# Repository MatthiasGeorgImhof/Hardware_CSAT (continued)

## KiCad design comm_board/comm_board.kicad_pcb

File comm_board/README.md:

# Communication Board #

Communication board with ethernet and radio operating in the US ISM band of 915MHz. Check your jurisdiction about availability of this band!

- STM32L496 microprocessor
- TI CC1101 transceiver for 915MHz oeration and TI CC1190 power frontend
- Ethernet modem

OpenLST Reference Hardware

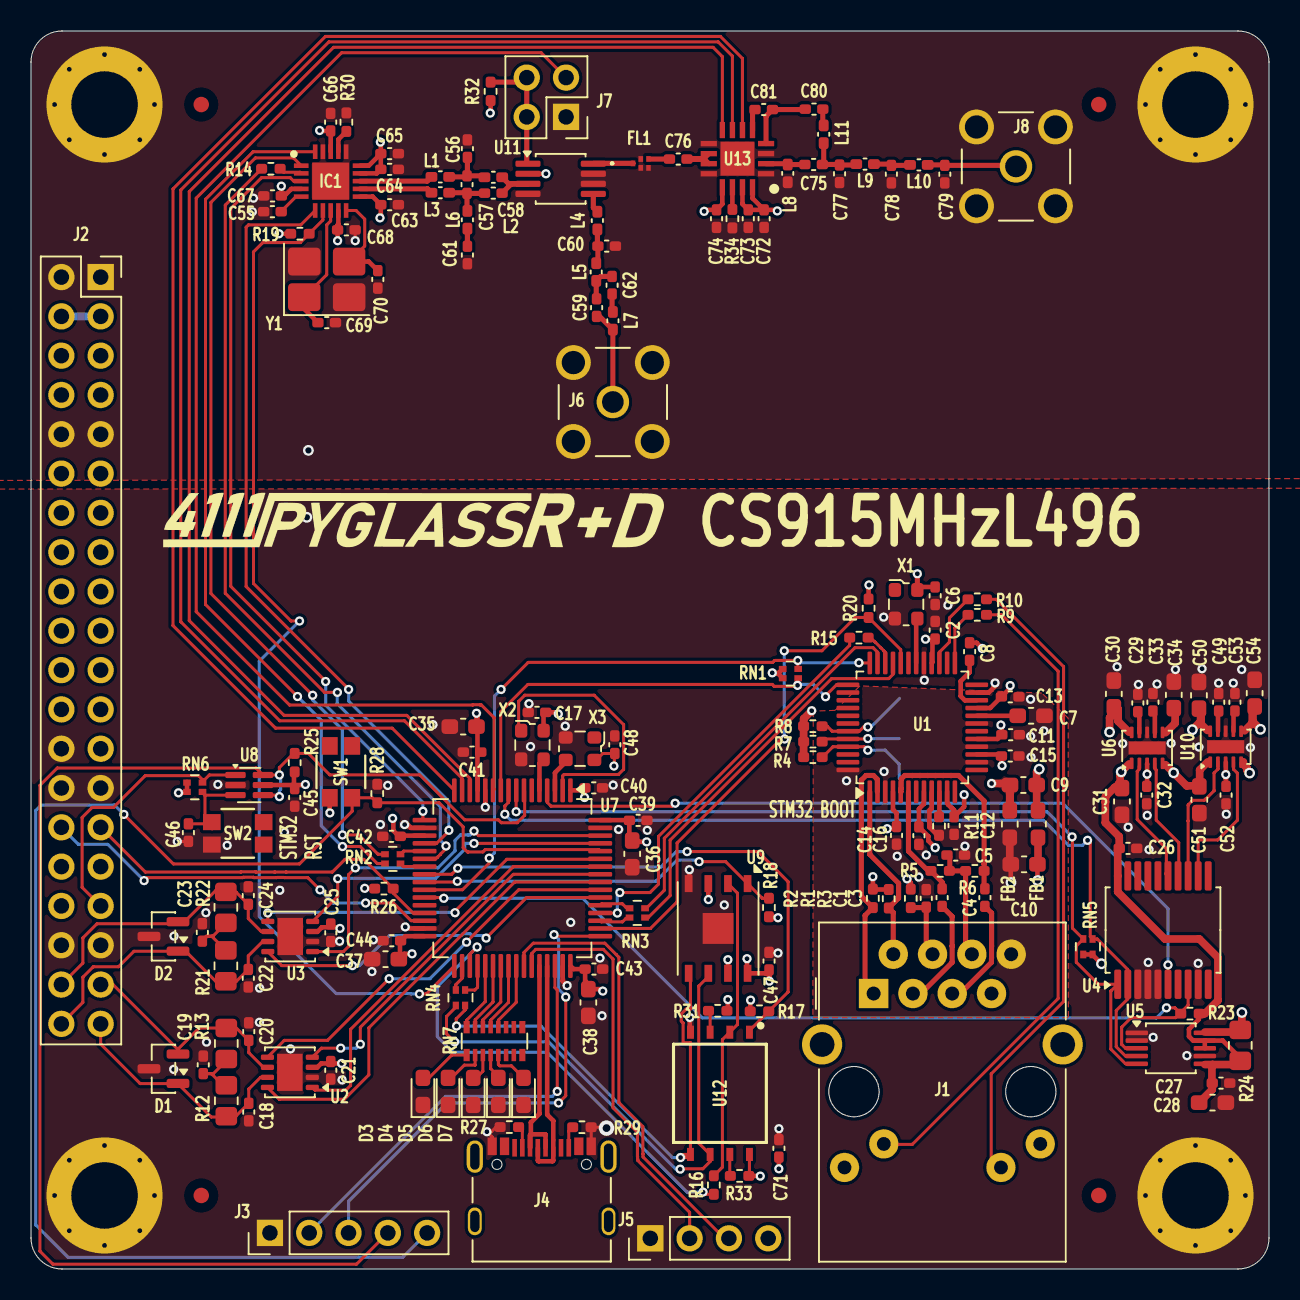
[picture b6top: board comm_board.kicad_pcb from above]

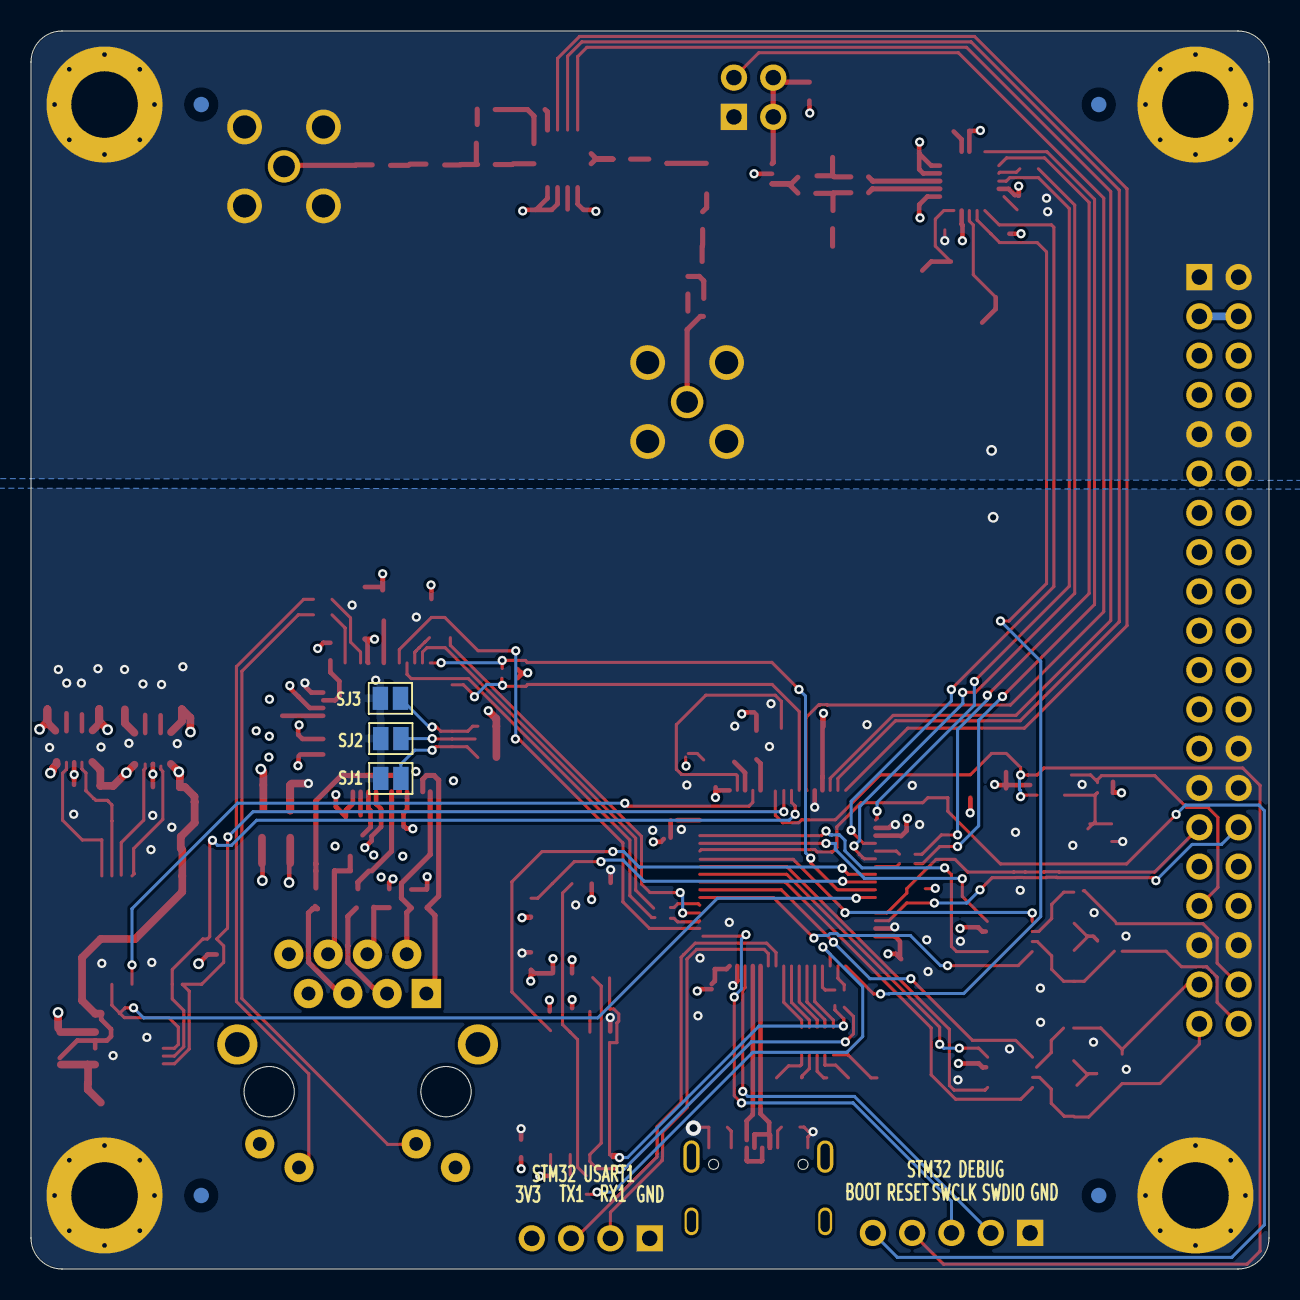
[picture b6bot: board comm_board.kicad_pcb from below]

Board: 4 copper layers, 80.0 x 80.0 mm, 186 parts (7 on the bottom side), 143 nets.

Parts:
C1, C5: 10nF; C_0402_1005Metric_Pad0.74x0.62mm_HandSolder
C2, C6, C8, C11, C12, C13, C14, C15, C16, C17, C21, C25, C26, C27, C32, C39, C40, C41, C42, C43, C44, C45, C46, C47, C48, C52, C71: 100nF; C_0402_1005Metric_Pad0.74x0.62mm_HandSolder
C3, C4: 6.8nF; C_0402_1005Metric_Pad0.74x0.62mm_HandSolder
C7, C9, C10, C28, C30, C34, C35, C36, C37, C38, C50, C54: 10uF; C_0603_1608Metric_Pad1.08x0.95mm_HandSolder
C18, C20, C22, C24: 100pF; C_0402_1005Metric_Pad0.74x0.62mm_HandSolder
C19, C23: 4nF7; C_0402_1005Metric_Pad0.74x0.62mm_HandSolder
C29, C33, C49, C53: 220pF; C_0402_1005Metric_Pad0.74x0.62mm_HandSolder
C31, C51: 22uF; C_0603_1608Metric_Pad1.08x0.95mm_HandSolder
C55, C61, C63, C64, C65, C66, C67, C68, C72, C73, C74: 100n; C_0402_1005Metric_Pad0.74x0.62mm_HandSolder
C56, C58, C59, C62: 1p5; C_0402_1005Metric_Pad0.74x0.62mm_HandSolder
C57: 1p; C_0402_1005Metric_Pad0.74x0.62mm_HandSolder
C60, C77: 3p3; C_0402_1005Metric_Pad0.74x0.62mm_HandSolder
C69, C70: 27p; C_0402_1005Metric_Pad0.74x0.62mm_HandSolder
C75, C76: 47p; C_0402_1005Metric_Pad0.74x0.62mm_HandSolder
C78: 8p2; C_0402_1005Metric_Pad0.74x0.62mm_HandSolder
C79: 0p5; C_0402_1005Metric_Pad0.74x0.62mm_HandSolder
C80, C81: 12p; C_0402_1005Metric_Pad0.74x0.62mm_HandSolder
D1, D2: NUP2105LT1G; SOT-23
D3: RED; LED_0603_1608Metric_Pad1.05x0.95mm_HandSolder
D4: GREEN; LED_0603_1608Metric_Pad1.05x0.95mm_HandSolder
D5, D6, D7: YELLOW; LED_0603_1608Metric_Pad1.05x0.95mm_HandSolder
FB1, FB2: 1K; L_0603_1608Metric_Pad1.05x0.95mm_HandSolder
FID1, FID2, FID3, FID4, FID5, FID6, FID7, FID8: Fiducial; Fiducial_1mm_Mask2mm
FL1: B39921B2672P810
H1, H2, H3, H4: MountingHole_Pad; MountingHole_4.3mm_M4_Pad_Via_Custom
IC1: CC1101RGPR; QFN50P400X400X100-21N-D
J1: RJ45_Amphenol_RJMG1BD3B8K1ANR
J2: PC104 Conn_02x20_Odd_Even; PinSocket_2x20_P2.54mm_Vertical
J3: Conn_01x05_Pin Vertical; PinHeader_1x05_P2.54mm_Vertical
J4: 10155435-00011LF; AMPHENOL_10155435-00011LF
J5: Conn_01x04_Pin Vertical; PinHeader_1x04_P2.54mm_Vertical
J6, J8: SMA Jack; LINX_CONSMA001-G
J7: Conn_02x03_Odd_Even; PinHeader_2x02_P2.54mm_Vertical
L1, L3, L4, L5, L7: 12n; L_0402_1005Metric_Pad0.77x0.64mm_HandSolder
L2, L6: 18n; L_0402_1005Metric_Pad0.77x0.64mm_HandSolder
L8: 10n; L_0402_1005Metric_Pad0.77x0.64mm_HandSolder
L9: 2n2; L_0402_1005Metric_Pad0.77x0.64mm_HandSolder
L10: 3n9; L_0402_1005Metric_Pad0.77x0.64mm_HandSolder
L11: 7n5; L_0402_1005Metric_Pad0.77x0.64mm_HandSolder
R1, R2, R5, R6: 49R9; R_0402_1005Metric_Pad0.72x0.64mm_HandSolder
R3: 10R; R_0402_1005Metric_Pad0.72x0.64mm_HandSolder
R4, R7, R8: 10K; R_0402_1005Metric_Pad0.72x0.64mm_HandSolder
R9, R10: 470R; R_0402_1005Metric_Pad0.72x0.64mm_HandSolder
R11: 12K4; R_0402_1005Metric_Pad0.72x0.64mm_HandSolder
R12, R13, R21, R22: 60R4; R_0805_2012Metric_Pad1.20x1.40mm_HandSolder
R14, R15, R16: 22R; R_0402_1005Metric_Pad0.72x0.64mm_HandSolder
R17, R18, R19, R20, R23, R25, R28, R31, R32, R33: 100K; R_0402_1005Metric_Pad0.72x0.64mm_HandSolder
R24: 10m; R_0805_2012Metric_Pad1.20x1.40mm_HandSolder
R26: 330K; R_0402_1005Metric_Pad0.72x0.64mm_HandSolder
R27, R29: 5K1; R_0402_1005Metric_Pad0.72x0.64mm_HandSolder
R30: 56K; R_0402_1005Metric_Pad0.72x0.64mm_HandSolder
R34: 3K3; R_0402_1005Metric_Pad0.72x0.64mm_HandSolder
RN1: 10K; R_Array_Convex_2x0402_widepads
RN2, RN3, RN4: 22R; R_Array_Convex_2x0402_widepads
RN5: 5K6; R_Array_Convex_2x0402_widepads
RN6: 100K; R_Array_Convex_2x0402_widepads
RN7: 1K; R_Array_Convex_8x0602_widepads
SJ1, SJ2, SJ3: SOLDERJUMPERREFLOW_NOPASTE; SolderJumper-2_P1.3mm_Open_Pad1.0x1.5mm
SW1, SW2: EVP-AA602W; EVP602AA
U1: W5500; LQFP-48_7x7mm_P0.5mm
U2, U3: TCAN3414; VSON-8-1EP_3x3mm_P0.65mm_EP1.65x2.4mm
U4: MCP23008T-E/SS; SSOP-20_5.3x7.2mm_P0.65mm
U5: INA226AIDGSR; VSSOP-10_3x3mm_P0.5mm
U6, U10: TPS22968QDMGRQ1; WSON-10-1EP_2x3mm_P0.5mm_EP0.84x2.4mm
U7: STM32L496RGTx; LQFP-64_10x10mm_P0.5mm
U8: 74LVC2G07; SOT-363_SC-70-6
U9: MR25H10; DFN-8-1EP_6x5mm_P1.27mm_EP2x2mm
U11: PE4250MLI; MSOP-8_3x3mm_P0.65mm
U12: MT29F4G01ABAFDWB-IT:F TR; SON127P800X600X65-8N
U13: CC1190RGVR; QFN65P400X400X100-17N-D
X1: 25MHz; Oscillator_SMD_ECS_2520MV-xxx-xx-4Pin_2.5x2.0mm
X2: 10MHz; Oscillator_SMD_ECS_2520MV-xxx-xx-4Pin_2.5x2.0mm
X3: 32.768KHZ; Oscillator_SMD_ECS_2520MV-xxx-xx-4Pin_2.5x2.0mm
Y1: 26MHz; Crystal_SMD_3225-4Pin_3.2x2.5mm_HandSoldering

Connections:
/3V3_AUX: J2.15, R24.1, U5.10 (IN+)
/3V3_BRIDGE: C17.1, C21.1, C25.1, C35.1, C36.1, C37.1, C38.1, C39.1, C40.1, C41.1, C42.1, C43.1, C44.1, C45.2, C48.1, J2.13, J5.4, R25.1, R26.1, RN5.3 (R2.2), RN5.4 (R1.2), RN6.1 (R1.1), RN6.2 (R2.1), SW1.1, U2.3 (VCC), U3.3 (VCC), U7.1 (VBAT), U7.13 (VDDA), U7.19 (VDD), U7.32 (VDD), U7.48 (VDDUSB), U7.64 (VDD), U8.5 (VCC), X2.4 (VDD), X3.4 (VCC)
/3V3_COMM: C54.2, C63.1, C64.1, C65.1, C66.1, C67.1, C68.1, IC1.4 (DVDD), IC1.9 (AVDD_1), IC1.11 (AVDD_2), IC1.14 (AVDD_3), IC1.15 (AVDD_4), IC1.18 (DGUARD), R19.1, R32.1, U10.6 (VOUT2), U11.2 (V1)
/3V3_LAN: C2.1, C6.1, C9.1, C30.1, FB1.1, J1.L1, J1.L4, R4.1, R7.1, R8.1, R20.1, RN1.3 (R2.2), RN1.4 (R1.2), U1.28 (VDD), U6.10 (VOUT1), X1.4 (VCC)
/CAN Bridge/3V3_MRAM: C47.1, C50.1, C71.1, R17.1, R18.1, R31.1, R33.1, U9.3 (~WP), U9.7 (~HOLD), U9.8 (VDD), U10.10 (VOUT1), U12.8 (VCC)
/CAN Bridge/CAN1_H: C22.1, D2.1 (K), J2.40, R21.1, U3.7 (CANH)
/CAN Bridge/CAN1_L: C24.2, D2.2 (K), J2.38, R22.2, U3.6 (CANL)
/CAN Bridge/CAN2_H: C18.1, D1.1 (K), J2.39, R12.1, U2.7 (CANH)
/CAN Bridge/CAN2_L: C20.2, D1.2 (K), J2.37, R13.2, U2.6 (CANL)
/CAN Bridge/COMM1_RST: J2.33, RN6.4 (R1.2), U8.1 (IN1)
/CAN Bridge/Flash/SPI_CLK: RN4.1 (R1.1), U9.6 (SCK), U12.6 (SCK)
/CAN Bridge/Flash/SPI_MISO: R16.1, U9.2 (SO), U12.2 (SO/IO1)
/CAN Bridge/Flash/SPI_MOSI: RN4.2 (R2.1), U9.5 (SI), U12.5 (SI/IO0)
/CAN Bridge/I2C2_SCL: RN5.2 (R2.1), U4.1 (SCL), U5.5 (SCL), U7.8 (PC0)
/CAN Bridge/I2C2_SDA: RN5.1 (R1.1), U4.2 (SDA), U5.4 (SDA), U7.9 (PC1)
/CAN Bridge/PMIC/BOOT: J3.5, R28.1, SW1.2, U7.60 (PH3_BOOT0)
/CAN Bridge/PMIC/CAN1_RX: U3.4 (RXD), U7.61 (PB8)
/CAN Bridge/PMIC/CAN1_SHDN: U3.5 (SHTD), U7.59 (PB7)
/CAN Bridge/PMIC/CAN1_STB: U3.8 (STB), U7.54 (PD2)
/CAN Bridge/PMIC/CAN1_TX: U3.1 (TXD), U7.62 (PB9)
/CAN Bridge/PMIC/CAN2_RX: U2.4 (RXD), U7.57 (PB5)
/CAN Bridge/PMIC/CAN2_SHDN: U2.5 (SHTD), U7.55 (PB3)
/CAN Bridge/PMIC/CAN2_STB: U2.8 (STB), U7.56 (PB4)
/CAN Bridge/PMIC/CAN2_TX: U2.1 (TXD), U7.58 (PB6)
/CAN Bridge/PMIC/EXTI0: RN1.2 (R2.1), U1.36 (~INT), U7.26 (PB0)
/CAN Bridge/PMIC/EXTI3: IC1.3 (GDO2), U7.17 (PA3)
/CAN Bridge/PMIC/EXTI4: IC1.6 (GDO0_(ATEST)), U7.20 (PA4)
/CAN Bridge/PMIC/EXTI10: J2.29, R26.2, U7.29 (PB10)
/CAN Bridge/PMIC/EXTI11: J2.30, U7.30 (PB11)
/CAN Bridge/PMIC/FS_DN: J4.A7 (DN1_A), J4.B7 (DN2_B), U7.44 (PA11)
/CAN Bridge/PMIC/FS_DP: J4.A6 (DP1_A), J4.B6 (DP2_B), U7.45 (PA12)
/CAN Bridge/PMIC/HSE_EN: U7.2 (PC13), X2.1 (TRI-STATE)
/CAN Bridge/PMIC/HSE_IN: U7.5 (PH0), X2.3 (OUTPUT)
/CAN Bridge/PMIC/LED1: RN7.16 (R), U7.37 (PC6)
/CAN Bridge/PMIC/LED2: RN7.15 (R), U7.38 (PC7)
/CAN Bridge/PMIC/LED3: RN7.14 (R), U7.39 (PC8)
/CAN Bridge/PMIC/LED4: RN7.13 (R), U7.40 (PC9)
/CAN Bridge/PMIC/LED5: RN7.12 (R), U7.41 (PA8)
/CAN Bridge/PMIC/NRST: J3.4, R25.2, U7.7 (NRST), U8.4 (OUT2), U8.6 (OUT1)
/CAN Bridge/PMIC/OSC32_IN: U7.3 (PC14), X3.3 (OUT)
/CAN Bridge/PMIC/PA0: U7.14 (PA0), U13.8 (PA_EN)
/CAN Bridge/PMIC/PA1: U7.15 (PA1), U13.7 (LNA_EN)
/CAN Bridge/PMIC/PA2: U7.16 (PA2), U13.6 (HGM)
/CAN Bridge/PMIC/PC2: RN1.1 (R1.1), U1.37 (~RST), U7.10 (PC2)
/CAN Bridge/PMIC/PC3: J7.3, U7.11 (PC3)
/CAN Bridge/PMIC/RESET: C46.1, RN6.3 (R2.2), SW2.3, U8.3 (IN2)
/CAN Bridge/PMIC/SPI1_MISO: R14.2, U7.22 (PA6)
/CAN Bridge/PMIC/SPI1_MOSI: RN2.3 (R2.2), U7.23 (PA7)
/CAN Bridge/PMIC/SPI1_SCK: RN2.4 (R1.2), U7.21 (PA5)
/CAN Bridge/PMIC/SPI2_MISO: R16.2, U7.35 (PB14)
/CAN Bridge/PMIC/SPI2_MOSI: RN4.3 (R2.2), U7.36 (PB15)
/CAN Bridge/PMIC/SPI2_SCK: RN4.4 (R1.2), U7.34 (PB13)
/CAN Bridge/PMIC/SPI3_MISO: R15.1, U7.52 (PC11)
/CAN Bridge/PMIC/SPI3_MOSI: RN3.3 (R2.2), U7.53 (PC12)
/CAN Bridge/PMIC/SPI3_SCK: RN3.4 (R1.2), U7.51 (PC10)
/CAN Bridge/PMIC/SYS_JTMS_SWCLK: J3.3, U7.49 (PA14)
/CAN Bridge/PMIC/SYS_JTMS_SWDIO: J3.2, U7.46 (PA13)
/CAN Bridge/PMIC/USART1_RX: J5.2, U7.43 (PA10)
/CAN Bridge/PMIC/USART1_TX: J5.3, U7.42 (PA9)
/CAN Bridge/Power Switch/ENABLE0: U4.12 (GP0), U10.4 (ON2)
/CAN Bridge/Power Switch/ENABLE1: U4.13 (GP1), U10.2 (ON1)
/CAN Bridge/Power Switch/ENABLE2: U4.14 (GP2), U6.4 (ON2)
/CAN Bridge/Power Switch/ENABLE3: U4.15 (GP3), U6.2 (ON1)
/CAN Bridge/Power Switch/VBUS: C26.1, C27.1, C28.1, C31.1, C32.1, C51.1, C52.1, R23.1, R24.2, U4.20 (VDD), U5.6 (VS), U5.8 (VBUS), U5.9 (IN-), U6.1 (VIN1), U6.3 (VBIAS), U6.5 (VIN2), U10.1 (VIN1), U10.3 (VBIAS), U10.5 (VIN2)
/CAN Bridge/Power Switch/VOUT2: C34.2, U6.6 (VOUT2)
/CAN Bridge/Power_INT: R23.2, U4.8 (INT), U5.3 (ALERT), U7.27 (PB1)
/CAN Bridge/Power_RST: U4.6 (*RESET), U7.4 (PC15)
/CAN Bridge/SPI_FLASH_CS: R17.2, U7.24 (PC4), U12.1 (CS#)
/CAN Bridge/SPI_LAN_CS: R20.2, U1.32 (~SCS), U7.50 (PA15)
/CAN Bridge/SPI_LAN_MISO: R15.2, U1.34 (MISO)
/CAN Bridge/SPI_LAN_MOSI: RN3.2 (R2.1), U1.35 (MOSI)
/CAN Bridge/SPI_LAN_SCK: RN3.1 (R1.1), U1.33 (SCLK)
/CAN Bridge/SPI_MRAM_CS: R18.2, U7.25 (PC5), U9.1 (~CS)
/CAN Bridge/SPI_RF_CS: IC1.7 (CSN), R19.2, U7.33 (PB12)
/CAN Bridge/SPI_RF_MISO: IC1.2 (SO_(GDO1)), R14.1
/CAN Bridge/SPI_RF_MOSI: IC1.20 (SI), RN2.2 (R2.1)
/CAN Bridge/SPI_RF_SCK: IC1.1 (SCLK), RN2.1 (R1.1)
/GND: C2.2, C6.2, C9.2, C17.2, C18.2, C19.2, C20.1, C21.2, C22.2, C23.2, C24.1, C25.2, C26.2, C27.2, C28.2, C29.2, C30.2, C31.2, C32.2, C33.1, C34.1, C35.2, C36.2, C37.2, C38.2, C39.2, C40.2, C41.2, C42.2, C43.2, C44.2, C45.1, C46.2, C47.2, C48.2, C49.2, C50.2, C51.2, C52.2, C53.1, C54.1, C55.2, C56.1, C60.2, C61.2, C63.2, C64.2, C65.2, C66.2, C67.2, C68.2, C69.2, C70.2, C71.2, C72.2, C73.2, C74.2, C77.2, C78.2, C79.2, D1.3 (A), D2.3 (A), D3.1 (K), D4.1 (K), D5.1 (K), D6.1 (K), D7.1 (K), FB2.1, FL1.2 (GROUND_1), FL1.3 (GROUND_2), FL1.5 (GROUND_3), H1.1, H2.1, H3.1, H4.1, IC1.16 (GND_1), IC1.19 (GND_2), IC1.21 (GND_3), J2.1, J2.2, J2.9, J2.10, J2.26, J2.27, J2.28, J2.35, J2.36, J3.1, J4.A1_B12 (GND), J4.B1_A12 (GND__1), J5.1, J6.2 (Ext), J7.1, J8.2 (Ext), L8.1, R27.1, R28.2, R29.1, R30.2, R34.2, SJ1.2 (B), SJ2.2 (B), SJ3.2 (B), SW2.4, U1.23 (RSVD), U1.29 (GND), U2.2 (GND), U2.9 (GND), U3.2 (GND), U3.9 (GND), U4.3 (A2), U4.4 (A1), U4.5 (A0), U4.9 (VSS), U5.1 (A1), U5.2 (A0), U5.7 (GND), U6.8 (GND), U6.11 (TPAD), U7.12 (VSSA), U7.18 (VSS), U7.31 (VSS), U7.47 (VSS), U7.63 (VSS), U8.2 (GND), U9.4 (VSS), U9.9 (PAD), U10.8 (GND), U10.11 (TPAD), U11.4 (N/C_OR_GND), U11.6 (GND_1), U11.7 (GND_2), U12.4 (VSS), U13.1 (GND_1), U13.3 (GND_2), U13.9 (GND_3), U13.12 (GND_4), U13.17 (GND_5), X1.2 (GND), X2.2 (GND), X3.2 (GND), Y1.2 (G), Y1.4 (G)
/INTERBOARD_CONNECTOR2/BATT: J2.3, J2.4
/PW_RF_915MHz/RF_INOUT: FL1.1 (INPUT), U11.8 (RF2)
/SPI_LAN/AGND: C1.2, C5.2, C7.2, C8.2, C10.2, C11.2, C12.2, C13.2, C14.2, C15.2, C16.2, FB2.2, J1.R8, R11.2, U1.3 (AGND), U1.9 (AGND), U1.14 (AGND), U1.16 (AGND), U1.19 (AGND), U1.48 (AGND)
/SPI_LAN/AVDD: C10.1, C11.1, C12.1, C13.1, C14.1, C15.1, C16.1, FB1.2, R1.1, R2.1, R3.1, U1.4 (AVDD), U1.8 (AVDD), U1.11 (AVDD), U1.15 (AVDD), U1.17 (AVDD), U1.21 (AVDD)
/SPI_LAN/GREENLED: J1.L3, R9.1
/SPI_LAN/RX+: C3.2, R5.2, U1.6 (RXP)
/SPI_LAN/RX-: C4.2, R6.2, U1.5 (RXN)
/SPI_LAN/TX+: J1.R1 (TD+), R2.2, U1.2 (TXP)
/SPI_LAN/TX-: J1.R2 (TD-), R1.2, U1.1 (TXN)
/SPI_LAN/YELLOWLED: J1.L2, R10.1
/VRF: C72.1, C73.1, C74.1, J2.5, U13.13 (VDD_LNA), U13.15 (VDD_PA2), U13.16 (VDD_PA1)
unnamed: C19.1, R12.2, R13.1
unnamed: C23.1, R21.2, R22.1
unnamed: C56.2, C57.1, L1.2, L2.1
unnamed: C57.2, C58.1, L3.2, L6.1
unnamed: C59.1, C62.1, L5.2
unnamed: C60.1, L4.2, L5.1
unnamed: C61.1, L6.2
unnamed: C62.2, L7.1
unnamed: C75.2, C77.1, L9.1, L11.1
unnamed: C78.1, L9.2, L10.1
unnamed: C80.1, L11.2
unnamed: D3.2 (A), RN7.1 (R)
unnamed: D4.2 (A), RN7.2 (R)
unnamed: D5.2 (A), RN7.3 (R)
unnamed: D6.2 (A), RN7.4 (R)
unnamed: D7.2 (A), RN7.5 (R)
unnamed: C76.1, FL1.4 (OUTPUT)
unnamed: C55.1, IC1.5 (DCOUPL)
unnamed: IC1.17 (RBIAS), R30.1
unnamed: IC1.13 (RF_N), L1.1
unnamed: IC1.12 (RF_P), L3.1
unnamed: C69.1, IC1.8 (XOSC_Q1), Y1.1
unnamed: C70.1, IC1.10 (XOSC_Q2), Y1.3
unnamed: C4.1, J1.R5 (RCT)
unnamed: C3.1, J1.R3 (RD+)
unnamed: C5.1, J1.R6 (RD-), R5.1, R6.1
unnamed: C1.1, J1.R4 (TCT), R3.2
unnamed: J4.A5 (CC1_A), R27.2
unnamed: J4.B5 (CC2_B), R29.2
unnamed: C59.2, J6.1 (In), L7.2
unnamed: J7.2, J7.4, R32.2, U11.1 (V2/DIR)
unnamed: C79.1, J8.1 (In), L10.2
unnamed: R4.2, SJ1.1 (A), U1.45 (PMODE0)
unnamed: R7.2, SJ2.1 (A), U1.44 (PMODE1)
unnamed: R8.2, SJ3.1 (A), U1.43 (PMODE2)
unnamed: C8.1, U1.22 (1V2O)
unnamed: R10.2, U1.27 (ACTLED)
unnamed: R11.1, U1.10 (EXRES1)
unnamed: R9.2, U1.25 (LINKLED)
unnamed: C7.1, U1.20 (TOCAP)
unnamed: U1.30 (XI/CLKIN), X1.3 (OUT)
unnamed: C29.1, U6.9 (CT1)
unnamed: C33.2, U6.7 (CT2)
unnamed: C49.1, U10.9 (CT1)
unnamed: C53.2, U10.7 (CT2)
unnamed: L4.1, U11.5 (RF1)
unnamed: C58.2, L2.2, U11.3 (RFC)
unnamed: R33.2, U12.7 (HOLD#/IO3)
unnamed: R31.2, U12.3 (WP#/IO2)
unnamed: R34.1, U13.14 (BIAS)
unnamed: C81.1, U13.5 (LNA_IN)
unnamed: C76.2, U13.10 (LNA_OUT), U13.11 (PA_IN)
unnamed: C75.1, L8.2, U13.2 (PA_OUT)
unnamed: C80.2, C81.2, U13.4 (TR_SW)

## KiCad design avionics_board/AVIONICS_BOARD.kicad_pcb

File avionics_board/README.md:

# Avionics board #
- STM32L496 controller
- IMU and magenetometer
- UART for GPS receiver
- Magnetorquer controllers
- Temperature sensors
- Sun detectors

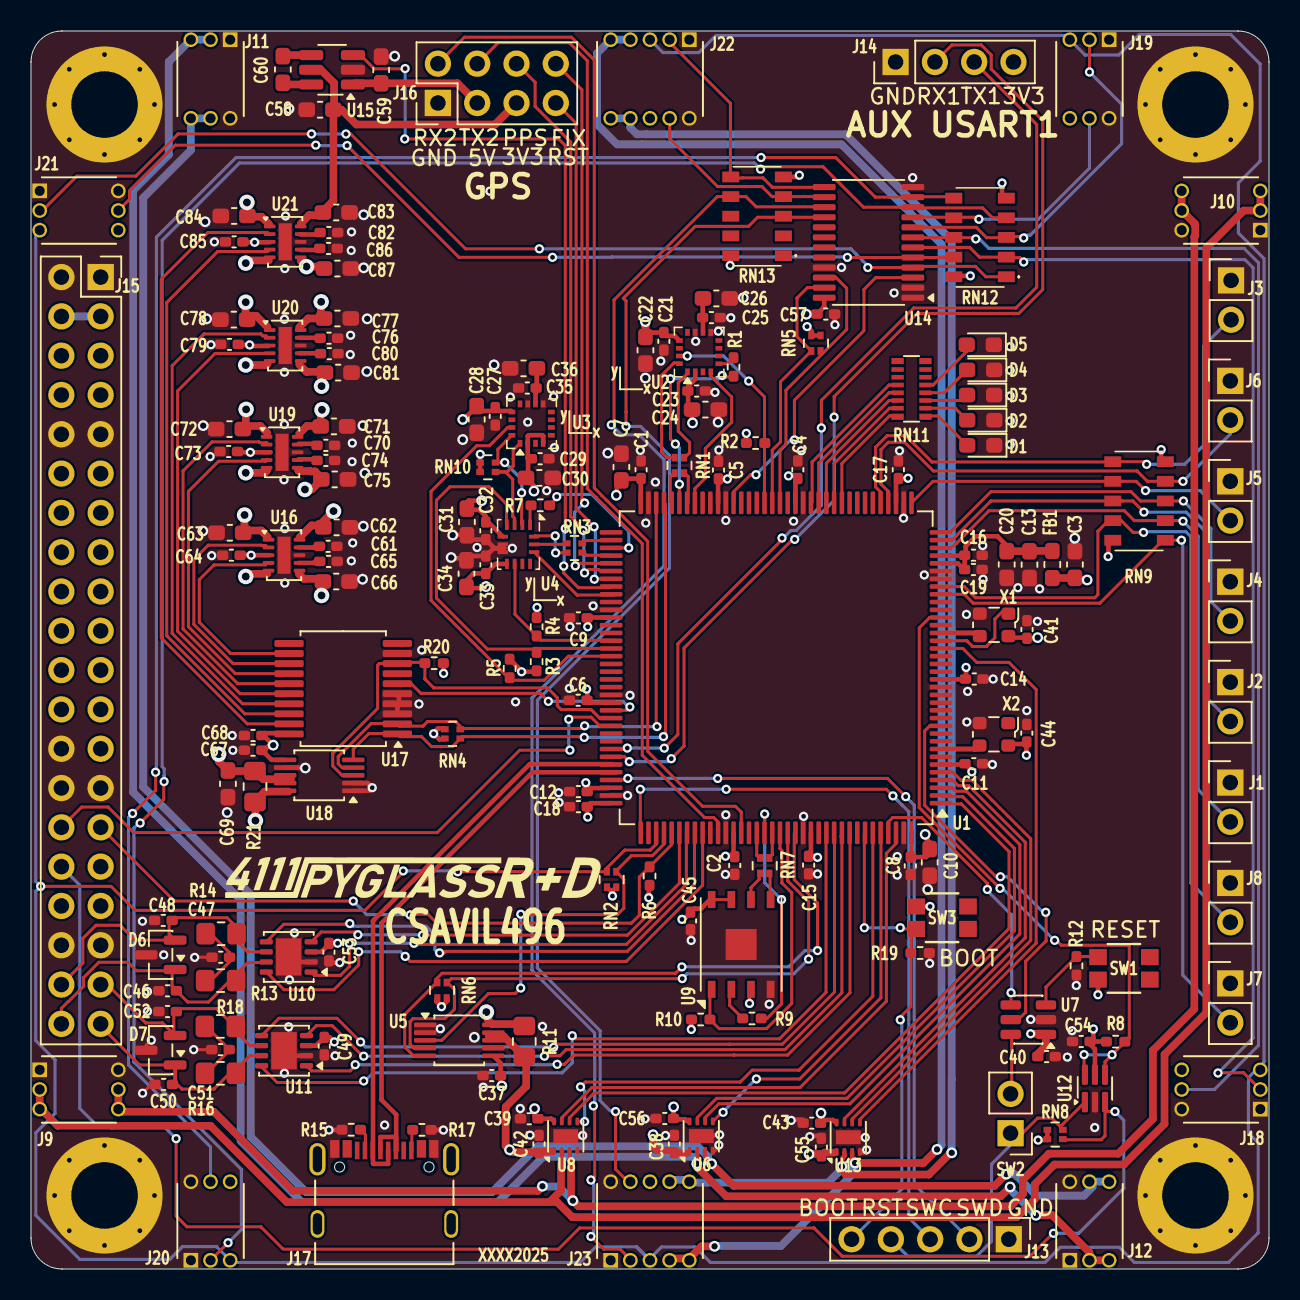
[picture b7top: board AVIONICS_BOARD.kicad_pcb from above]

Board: 4 copper layers, 80.0 x 80.0 mm, 182 parts (0 on the bottom side), 161 nets.

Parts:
C1, C2, C4, C5, C6, C8, C9, C11, C12, C14, C15, C16, C17, C18, C19, C21, C23, C25, C27, C29, C32, C33, C35, C37, C38, C39, C40, C41, C42, C43, C44, C45, C49, C53, C54, C55, C56, C57, C64, C67, C68, C73, C79, C85: 100nF; C_0402_1005Metric_Pad0.74x0.62mm_HandSolder
C3, C7, C10, C13, C20, C22, C24, C26, C28, C30, C31, C34, C36, C58, C59, C62, C66, C69, C71, C75, C77, C81, C83, C87: 10uF; C_0603_1608Metric_Pad1.08x0.95mm_HandSolder
C46, C48, C50, C52: 100pF; C_0402_1005Metric_Pad0.74x0.62mm_HandSolder
C47, C51: 4nF7; C_0402_1005Metric_Pad0.74x0.62mm_HandSolder
C60: 1uF; C_0603_1608Metric_Pad1.08x0.95mm_HandSolder
C61, C65, C70, C74, C76, C80, C82, C86: 220pF; C_0402_1005Metric_Pad0.74x0.62mm_HandSolder
C63, C72, C78, C84: 22uF; C_0603_1608Metric_Pad1.08x0.95mm_HandSolder
D1: RED; LED_0603_1608Metric_Pad1.05x0.95mm_HandSolder
D2: GREEN; LED_0603_1608Metric_Pad1.05x0.95mm_HandSolder
D3, D4, D5: YELLOW; LED_0603_1608Metric_Pad1.05x0.95mm_HandSolder
D6, D7: NUP2105LT1G; SOT-23
FB1: 120R; L_0603_1608Metric_Pad1.05x0.95mm_HandSolder
H1, H2, H3, H4: MountingHole_Pad; MountingHole_4.3mm_M4_Pad_Via_Custom
J1, J2, J3, J4, J5, J6, J7, J8: Conn_01x02_Pin Vertical; PinHeader_1x02_P2.54mm_Vertical
J9, J10, J11, J12, J18, J19, J20, J21: Conn_02x03_Odd_Even; HARWIN_M50-3200345
J13: Conn_01x05_Pin Vertical; PinHeader_1x05_P2.54mm_Vertical
J14: Conn_01x04_Pin Vertical; PinHeader_1x04_P2.54mm_Vertical
J15: PC104 Conn_02x20_Odd_Even; PinSocket_2x20_P2.54mm_Vertical
J16: Conn_02x04; PinHeader_2x04_P2.54mm_Vertical
J17: 10155435-00011LF; AMPHENOL_10155435-00011LF
J22, J23: Conn_02x05_Odd_Even; HARWIN_M50-3200545
R1, R7, R9: 22R; R_0402_1005Metric_Pad0.72x0.64mm_HandSolder
R2, R3, R4, R5, R8, R10, R19, R20: 100K; R_0402_1005Metric_Pad0.72x0.64mm_HandSolder
R6: 330K; R_0402_1005Metric_Pad0.72x0.64mm_HandSolder
R11, R21: 10m; R_0805_2012Metric_Pad1.20x1.40mm_HandSolder
R12: 22K; R_0402_1005Metric_Pad0.72x0.64mm_HandSolder
R13, R14, R16, R18: 60R4; R_0805_2012Metric_Pad1.20x1.40mm_HandSolder
R15, R17: 5K1; R_0402_1005Metric_Pad0.72x0.64mm_HandSolder
RN1, RN3, RN7: 22R; R_Array_Convex_2x0402_widepads
RN2, RN8: 100K; R_Array_Convex_2x0402_widepads
RN4, RN5, RN6, RN10: 5K6; R_Array_Convex_2x0402_widepads
RN9: 22K; R_Array_Concave_5x2512_widepads
RN11: 1K; R_Array_Convex_8x0602_widepads
RN12, RN13: 5K6; R_Array_Concave_5x2512_widepads
SW1, SW3: EVP-AA602W; EVP602AA
SW2: Conn_01x02_Pin Vertical; PinHeader_1x02_P2.54mm_Vertical
U1: STM32L496ZGTx; LQFP-144_20x20mm_P0.5mm
U2, U3: MMC5983MA; LGA-16_3x3mm_P0.5mm
U4: BMI270; Bosch_LGA-14_3x2.5mm_P0.5mm
U5, U18: INA226; VSSOP-10_3x3mm_P0.5mm
U6, U8, U13: DRV8838; WSON-8-1EP_2x2mm_P0.5mm_EP0.9x1.6mm
U7: TPL5010; SOT-23-6
U9: MR25H10; DFN-8-1EP_6x5mm_P1.27mm_EP2x2mm
U10, U11: TCAN3414; VSON-8-1EP_3x3mm_P0.65mm_EP1.65x2.4mm
U12: 74LVC2G07; SOT-363_SC-70-6
U14: TCA9548APWR; TSSOP-24_4.4x7.8mm_P0.65mm
U15: AP3602AKTR-G1; SOT-23-6_Handsoldering
U16, U19, U20, U21: TPS22968QDMGRQ1; WSON-10-1EP_2x3mm_P0.5mm_EP0.84x2.4mm
U17: MCP23008T-E/SS; SSOP-20_5.3x7.2mm_P0.65mm
X1: 10MHz; Oscillator_SMD_ECS_2520MV-xxx-xx-4Pin_2.5x2.0mm
X2: 32.768KHZ; Oscillator_SMD_ECS_2520MV-xxx-xx-4Pin_2.5x2.0mm

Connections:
/3V3_ACS_LOGIC: C37.1, C39.1, C43.1, C56.1, C66.2, RN6.3 (R2.2), RN6.4 (R1.2), U5.6 (VS), U6.8 (VCC), U8.8 (VCC), U13.8 (VCC), U16.6 (VOUT2)
/3V3_AUX: C67.1, C68.1, J15.11, R20.1, R21.1, RN4.3 (R2.2), RN4.4 (R1.2), U17.20 (VDD), U18.6 (VS), U18.10 (IN+)
/3V3_CLK: C41.1, C71.1, U19.10 (VOUT1), X1.4 (VDD)
/3V3_GPS: C58.1, C83.1, J16.5, U15.5 (VIN), U21.10 (VOUT1)
/3V3_GYRO: C27.2, C28.1, C29.2, C30.1, C31.1, C32.1, C33.1, C34.1, C75.2, RN10.3 (R2.2), RN10.4 (R1.2), U3.2 (VDD), U3.4 (SPI_CS), U3.13 (VDDIO), U4.5 (VDDIO), U4.8 (VDD), U19.6 (VOUT2)
/3V3_MAG: C21.2, C22.1, C23.2, C24.1, C77.1, U2.2 (VDD), U2.13 (VDDIO), U20.10 (VOUT1)
/3V3_MRAM: C45.1, C62.1, R10.2, U9.3 (~WP), U9.7 (~HOLD), U9.8 (VDD), U16.10 (VOUT1)
/3V3_STM_CORE: C1.1, C2.1, C3.1, C4.1, C5.2, C6.1, C7.2, C8.2, C9.2, C10.2, C11.1, C12.2, C14.1, C15.2, C17.1, C18.2, C40.1, C44.1, C49.1, C53.1, C54.2, FB1.1, J14.4, J15.12, R2.1, R3.1, R4.1, R5.1, R6.1, R8.1, RN2.3 (R2.2), RN2.4 (R1.2), RN8.1 (R1.1), RN8.2 (R2.1), SW1.2, SW3.1, U1.6 (VBAT), U1.17 (VDD), U1.39 (VDD), U1.52 (VDD), U1.62 (VDD), U1.72 (VDD), U1.84 (VDD), U1.95 (VDDIO2), U1.106 (VDDUSB), U1.108 (VDD), U1.121 (VDD), U1.131 (VDDIO2), U1.144 (VDD), U7.1 (VDD), U10.3 (VCC), U11.3 (VCC), U12.5 (VCC), X2.4 (VCC)
/3V3_SUN: C57.1, C87.2, J18.6, J19.6, J20.6, J21.6, J22.6, J23.6, RN5.3 (R2.2), RN5.4 (R1.2), RN12.5, RN12.10, RN13.5, RN13.10, U14.24 (VCC), U21.6 (VOUT2)
/3V3_TEMP: C81.2, RN9.5, RN9.10, U20.6 (VOUT2)
/5V_ACS_COIL: J15.7, R11.1, U5.10 (Vin+)
/*ATTENTION: J15.29, R6.2, U1.113 (PC12)
/*AVI_RST: J15.32, RN8.3 (R2.2), U12.3 (IN2)
/*EPS_RST: J15.30, U1.98 (PC8)
/ACS/PWR_DRIVER: C38.1, C42.1, C55.1, R11.2, U5.8 (Vbus), U5.9 (Vin-), U6.1 (VM), U8.1 (VM), U13.1 (VM)
/ACS/X_N: J9.4, J9.6, J10.4, J10.6, U8.3 (OUT2)
/ACS/X_P: J9.3, J9.5, J10.3, J10.5, U8.2 (OUT1)
/ACS/Y_N: J11.4, J11.6, J12.4, J12.6, U6.3 (OUT2)
/ACS/Y_P: J11.3, J11.5, J12.3, J12.5, U6.2 (OUT1)
/ACS_INT: RN2.1 (R1.1), U1.112 (PC11), U5.3 (~Alert)
/ACS_X_PH: U1.1 (PE2), U8.6 (PH)
/ACS_X_SLEEP: U1.142 (PE1), U8.7 (~SLEEP)
/ACS_Y_PH: U1.3 (PE4), U6.6 (PH)
/ACS_Y_SLEEP: U1.2 (PE3), U6.7 (~SLEEP)
/ACS_Z_PH: U1.5 (PE6), U13.6 (PH)
/ACS_Z_SLEEP: U1.4 (PE5), U13.7 (~SLEEP)
/ADC1_IN3: J7.2, RN9.1, U1.28 (PC2)
/ADC1_IN4: J8.2, RN9.9, U1.29 (PC3)
/ADC1_IN5: J1.2, RN9.2, U1.34 (PA0)
/ADC1_IN6: J2.2, RN9.8, U1.35 (PA1)
/ADC1_IN7: J4.2, RN9.3, U1.36 (PA2)
/ADC1_IN8: J5.2, RN9.7, U1.37 (PA3)
/ADC1_IN9: J6.2, RN9.4, U1.40 (PA4)
/ADC1_IN10: J3.2, RN9.6, U1.41 (PA5)
/AUX POWER/ENABLE_0: U16.4 (ON2), U17.12 (GP0)
/AUX POWER/ENABLE_1: U16.2 (ON1), U17.13 (GP1)
/AUX POWER/ENABLE_2: U17.14 (GP2), U19.4 (ON2)
/AUX POWER/ENABLE_3: U17.15 (GP3), U19.2 (ON1)
/AUX POWER/ENABLE_4: U17.16 (GP4), U20.4 (ON2)
/AUX POWER/ENABLE_5: U17.17 (GP5), U20.2 (ON1)
/AUX POWER/ENABLE_6: U17.18 (GP6), U21.4 (ON2)
/AUX POWER/ENABLE_7: U17.19 (GP7), U21.2 (ON1)
/AUX POWER/VBUS: C63.1, C64.1, C69.1, C72.1, C73.1, C78.1, C79.1, C84.1, C85.1, R21.2, U16.1 (VIN1), U16.3 (VBIAS), U16.5 (VIN2), U18.8 (VBUS), U18.9 (IN-), U19.1 (VIN1), U19.3 (VBIAS), U19.5 (VIN2), U20.1 (VIN1), U20.3 (VBIAS), U20.5 (VIN2), U21.1 (VIN1), U21.3 (VBIAS), U21.5 (VIN2)
/CAN1_H: C46.1, D6.1 (K), J15.40, R13.1, U10.7 (CANH)
/CAN1_L: C48.2, D6.2 (K), J15.38, R14.2, U10.6 (CANL)
/CAN2_H: C50.1, D7.1 (K), J15.39, R16.1, U11.7 (CANH)
/CAN2_L: C52.2, D7.2 (K), J15.37, R18.2, U11.6 (CANL)
/GPS_INTERFACE/CAN_POWER6/VOUT: C59.1, J16.3, U15.1 (VOUT)
/GPS_INTERFACE/FIX: J16.8, U1.77 (PD8)
/GPS_INTERFACE/PPS: J16.6, U1.78 (PD9)
/GPS_INTERFACE/RESET: J16.7, U1.79 (PD10)
/GPS_INTERFACE/SHDN_5V: U1.80 (PD11), U15.3 (*SHDN)
/GPS_INTERFACE/UART_RX: J16.2, U1.122 (PD6)
/GPS_INTERFACE/UART_TX: J16.4, U1.119 (PD5)
/GYRO1_INT: R3.2, U1.88 (PG3), U4.4 (INT1)
/GYRO2_INT: R4.2, U1.87 (PG2), U4.9 (INT2)
/GYRO/SCL: RN10.1 (R1.1), U3.1 (SCL/SPI_SCK), U4.3 (ASCx)
/GYRO/SDA: RN10.2 (R2.1), U3.16 (SDA/SPI_SDI), U4.2 (ASDx)
/GYROAUX_INT: R5.2, U1.89 (PG4), U3.15 (INT)
/GYRO_CS: U1.81 (PD12), U4.12 (CSB)
/I2C1_SCL: RN6.2 (R2.1), U1.129 (PG14), U5.5 (SCL)
/I2C1_SDA: RN6.1 (R1.1), U1.128 (PG13), U5.4 (SDA)
/I2C2_SCL: RN4.1 (R1.1), U1.69 (PB10), U17.1 (SCL), U18.5 (SCL)
/I2C2_SDA: RN4.2 (R2.1), U1.70 (PB11), U17.2 (SDA), U18.4 (SDA)
/I2C4_SCL: RN5.2 (R2.1), U1.54 (PF14), U14.22 (SCL)
/I2C4_SDA: RN5.1 (R1.1), U1.55 (PF15), U14.23 (SDA)
/INTERBOARD_CONNECTOR/BATT: J15.3, J15.4
/MAG_CS: U1.65 (PE12), U2.4 (SPI_CS)
/MAG_INT: R2.2, U1.56 (PG0), U2.15 (INT)
/Power_INT: R20.2, U1.97 (PC7), U17.8 (INT), U18.3 (ALERT)
/Power_RST: U1.96 (PC6), U17.6 (*RESET)
/RST_SUN: U1.60 (PE9), U14.3 (~RESET)
/SPI1_MISO: R1.1, U2.5 (SPI_SDO)
/SPI1_MOSI: RN1.2 (R2.1), U2.16 (SDA/SPI_SDI)
/SPI1_SCK: RN1.1 (R1.1), U2.1 (SCL/SPI_SCK)
/SPI2_MISO: R7.1, U4.1 (SDO)
/SPI2_MOSI: RN3.2 (R2.1), U4.14 (SDx)
/SPI2_SCK: RN3.1 (R1.1), U4.13 (SCx)
/STM32L4/10MHZ_OE: U1.22 (PF10), X1.1 (TRI-STATE)
/STM32L4/BOOT0: J13.5, R19.1, SW3.2, U1.138 (PH3)
/STM32L4/CAN1_RX: U1.114 (PD0), U10.4 (RXD)
/STM32L4/CAN1_SHDN: U1.116 (PD2), U10.5 (SHTD)
/STM32L4/CAN1_STB: U1.117 (PD3), U10.8 (STB)
/STM32L4/CAN1_TX: U1.115 (PD1), U10.1 (TXD)
/STM32L4/CAN2_RX: U1.135 (PB5), U11.4 (RXD)
/STM32L4/CAN2_SHDN: U1.134 (PB4), U11.5 (SHTD)
/STM32L4/CAN2_STB: U1.133 (PB3), U11.8 (STB)
/STM32L4/CAN2_TX: U1.136 (PB6), U11.1 (TXD)
/STM32L4/JTCK_SWCLK: J13.3, U1.109 (PA14)
/STM32L4/JTMS_SWDIO: J13.2, U1.105 (PA13)
/STM32L4/LED_1: RN11.16 (R), U1.46 (PB0)
/STM32L4/LED_2: RN11.15 (R), U1.47 (PB1)
/STM32L4/LED_3: RN11.14 (R), U1.48 (PB2)
/STM32L4/LED_4: RN11.13 (R), U1.49 (PF11)
/STM32L4/LED_5: RN11.12 (R), U1.50 (PF12)
/STM32L4/MRAM/SPI_MISO: R9.2, U9.2 (SO)
/STM32L4/MRAM/SPI_MOSI: RN7.4 (R1.2), U9.5 (SI)
/STM32L4/MRAM/SPI_SCK: RN7.3 (R2.2), U9.6 (SCK)
/STM32L4/MRAM_CS: R10.1, U1.127 (PG12), U9.1 (~CS)
/STM32L4/NRST: R8.2, U1.25 (NRST), U12.4 (OUT2), U12.6 (OUT1)
/STM32L4/RCC_OSC32_IN: U1.8 (PC14), X2.3 (OUT)
/STM32L4/RCC_OSC_IN: U1.23 (PH0), X1.3 (OUTPUT)
/STM32L4/RST: J13.4, RN8.4 (R1.2), SW2.1, U12.1 (IN1)
/STM32L4/SPI1_MISO: R1.2, U1.67 (PE14)
/STM32L4/SPI1_MOSI: RN1.3 (R2.2), U1.68 (PE15)
/STM32L4/SPI1_SCK: RN1.4 (R1.2), U1.66 (PE13)
/STM32L4/SPI2_MISO: R7.2, U1.75 (PB14)
/STM32L4/SPI2_MOSI: RN3.3 (R2.2), U1.76 (PB15)
/STM32L4/SPI2_SCK: RN3.4 (R1.2), U1.74 (PB13)
/STM32L4/SPI3_MISO: R9.1, U1.125 (PG10)
/STM32L4/SPI3_MOSI: RN7.1 (R1.1), U1.126 (PG11)
/STM32L4/SPI3_SCK: RN7.2 (R2.1), U1.124 (PG9)
/STM32L4/USART1_RX: J14.2, U1.102 (PA10)
/STM32L4/USART1_TX: J14.3, U1.101 (PA9)
/STM32L4/USB/DN: J17.A7 (DN1_A), J17.B7 (DN2_B), U1.103 (PA11)
/STM32L4/USB/DP: J17.A6 (DP1_A), J17.B6 (DP2_B), U1.104 (PA12)
/STM32L4/VDDA: C13.1, C16.1, C19.2, C20.2, FB1.2, U1.32 (VREF+), U1.33 (VDDA)
/STM32L4/WATCHDOG_DONE: U1.141 (PE0), U7.4 (DONE)
/STM32L4/WATCHDOG_WAKE: U1.11 (PF1), U7.5 (WAKE)
/SUN_INT: J18.5, J19.5, J20.5, J21.5, J22.5, J23.5, RN2.2 (R2.1), U1.111 (PC10)
/Solar Sensors/SC0: J21.4, RN12.9, U14.5 (SC0)
/Solar Sensors/SC1: J18.4, RN12.8, U14.7 (SC1)
/Solar Sensors/SC2: J19.4, RN12.7, U14.9 (SC2)
/Solar Sensors/SC3: J20.4, RN12.6, U14.11 (SC3)
/Solar Sensors/SC4: J22.4, RN13.4, U14.14 (SC4)
/Solar Sensors/SC5: J23.4, RN13.3, U14.16 (SC5)
/Solar Sensors/SD0: J21.3, RN12.1, U14.4 (SD0)
/Solar Sensors/SD1: J18.3, RN12.2, U14.6 (SD1)
/Solar Sensors/SD2: J19.3, RN12.3, U14.8 (SD2)
/Solar Sensors/SD3: J20.3, RN12.4, U14.10 (SD3)
/Solar Sensors/SD4: J22.3, RN13.6, U14.13 (SD4)
/Solar Sensors/SD5: J23.3, RN13.7, U14.15 (SD5)
/TIM15_CH1: U1.21 (PF9), U13.5 (EN)
/TIM16_CH1: U1.139 (PB8), U8.5 (EN)
/TIM17_CH1: U1.140 (PB9), U6.5 (EN)
GND: C1.2, C2.2, C3.2, C4.2, C5.1, C6.2, C7.1, C8.1, C9.1, C10.1, C11.2, C12.1, C13.2, C14.2, C15.1, C16.2, C17.2, C18.1, C19.1, C20.1, C21.1, C22.2, C23.1, C24.2, C25.1, C26.1, C27.1, C28.2, C29.1, C30.2, C31.2, C32.2, C33.2, C34.2, C35.1, C36.1, C37.2, C38.2, C39.2, C40.2, C41.2, C42.2, C43.2, C44.2, C45.2, C46.2, C47.2, C48.1, C49.2, C50.2, C51.2, C52.1, C53.2, C54.1, C55.2, C56.2, C57.2, C58.2, C59.2, C61.2, C62.2, C63.2, C64.2, C65.1, C66.1, C67.2, C68.2, C69.2, C70.2, C71.2, C72.2, C73.2, C74.1, C75.1, C76.2, C77.2, C78.2, C79.2, C80.1, C81.1, C82.2, C83.2, C84.2, C85.2, C86.1, C87.1, D1.1 (K), D2.1 (K), D3.1 (K), D4.1 (K), D5.1 (K), D6.3 (A), D7.3 (A), H1.1, H2.1, H3.1, H4.1, J1.1, J2.1, J3.1, J4.1, J5.1, J6.1, J7.1, J8.1, J9.1, J9.2, J10.1, J10.2, J11.1, J11.2, J12.1, J12.2, J13.1, J14.1, J15.1, J15.2, J15.9, J15.10, J15.26, J15.27, J15.28, J15.35, J15.36, J16.1, J17.A1_B12 (GND), J17.B1_A12 (GND__1), J18.1, J18.2, J19.1, J19.2, J20.1, J20.2, J21.1, J21.2, J22.1, J22.2, J23.1, J23.2, R12.2, R15.1, R17.1, R19.2, U1.16 (VSS), U1.30 (VSSA), U1.31 (VREF-), U1.38 (VSS), U1.51 (VSS), U1.61 (VSS), U1.71 (VSS), U1.83 (VSS), U1.94 (VSS), U1.107 (VSS), U1.120 (VSS), U1.130 (VSS), U1.143 (VSS), U2.9 (VSS), U2.11 (VSS), U3.9 (VSS), U3.11 (VSS), U4.6 (GNDIO), U4.7 (GND), U5.1 (A1), U5.2 (A0), U5.7 (GND), U6.4 (GND), U6.9 (GND), U7.2 (GND), U8.4 (GND), U8.9 (GND), U9.4 (VSS), U9.9 (PAD), U10.2 (GND), U10.9 (GND), U11.2 (GND), U11.9 (GND), U12.2 (GND), U13.4 (GND), U13.9 (GND), U14.1 (A0), U14.2 (A1), U14.12 (GND), U14.21 (A2), U15.2 (GND), U16.8 (GND), U16.11 (TPAD), U17.3 (A2), U17.4 (A1), U17.5 (A0), U17.9 (VSS), U18.1 (A1), U18.2 (A0), U18.7 (GND), U19.8 (GND), U19.11 (TPAD), U20.8 (GND), U20.11 (TPAD), U21.8 (GND), U21.11 (TPAD), X1.2 (GND), X2.2 (GND)
unnamed: C47.1, R13.2, R14.1
unnamed: C51.1, R16.2, R18.1
unnamed: D1.2 (A), RN11.1 (R)
unnamed: D2.2 (A), RN11.2 (R)
unnamed: D3.2 (A), RN11.3 (R)
unnamed: D4.2 (A), RN11.4 (R)
unnamed: D5.2 (A), RN11.5 (R)
unnamed: J17.A5 (CC1_A), R15.2
unnamed: J17.B5 (CC2_B), R17.2
unnamed: C25.2, C26.2, U2.10 (CAP)
unnamed: C35.2, C36.2, U3.10 (CAP)
unnamed: R12.1, SW1.1, U7.3 (DELAY/M_RST)
unnamed: SW2.2, U7.6 (~RST)
unnamed: C60.2, U15.6 (C+)
unnamed: C60.1, U15.4 (C-)
unnamed: C61.1, U16.9 (CT1)
unnamed: C65.2, U16.7 (CT2)
unnamed: C70.1, U19.9 (CT1)
unnamed: C74.2, U19.7 (CT2)
unnamed: C76.1, U20.9 (CT1)
unnamed: C80.2, U20.7 (CT2)
unnamed: C82.1, U21.9 (CT1)
unnamed: C86.2, U21.7 (CT2)
Z_N: J22.7, J22.9, J23.7, J23.9, U13.3 (OUT2)
Z_P: J22.8, J22.10, J23.8, J23.10, U13.2 (OUT1)
